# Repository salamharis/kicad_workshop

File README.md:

# KiCAD Workshop
Introduction on how to use KiCAD

Here the full slide for the workshop:
- [KiCAD Workshop Slides](https://docs.google.com/presentation/d/147WCcNicvjxVyRoyQiyZUYUu0onVnB6EPcWMXZ73EBk/edit?usp=sharing)

``` Disclaimer: This project only for educational purposes ```

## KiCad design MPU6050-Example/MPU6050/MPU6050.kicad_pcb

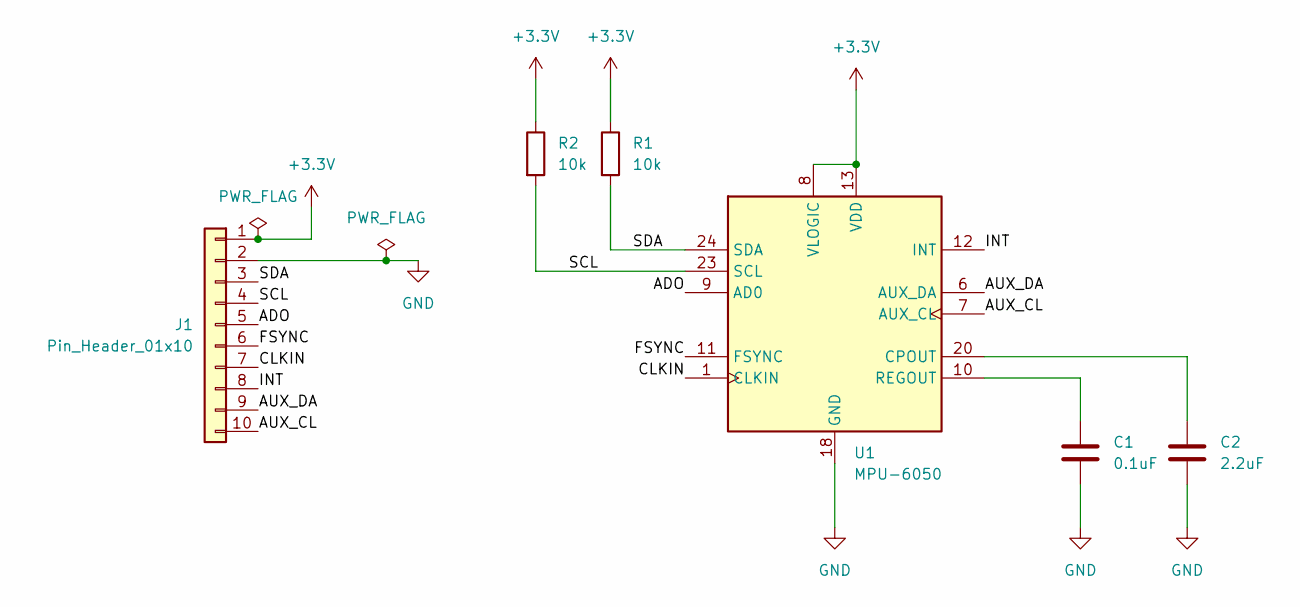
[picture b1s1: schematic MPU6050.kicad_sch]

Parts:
C1: 0.1uF; C_0603_1608Metric
C2: 2.2uF; C_0603_1608Metric
J1: Pin_Header_01x10; PinHeader_1x10_P2.54mm_Vertical
R1, R2: 10k; R_0603_1608Metric
U1: MPU-6050; InvenSense_QFN-24_4x4mm_P0.5mm

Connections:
+3.3V: J1.1, R1.1, R2.1, U1.8 (VLOGIC), U1.13 (VDD)
/ADO: J1.5, U1.9 (AD0)
/AUX_CL: J1.10, U1.7 (AUX_CL)
/AUX_DA: J1.9, U1.6 (AUX_DA)
/CLKIN: J1.7, U1.1 (CLKIN)
/FSYNC: J1.6, U1.11 (FSYNC)
/INT: J1.8, U1.12 (INT)
/SCL: J1.4, R2.2, U1.23 (SCL)
/SDA: J1.3, R1.2, U1.24 (SDA)
GND: C1.2, C2.2, J1.2, U1.18 (GND)
unnamed: C2.1, U1.20 (CPOUT)
unnamed: C1.1, U1.10 (REGOUT)

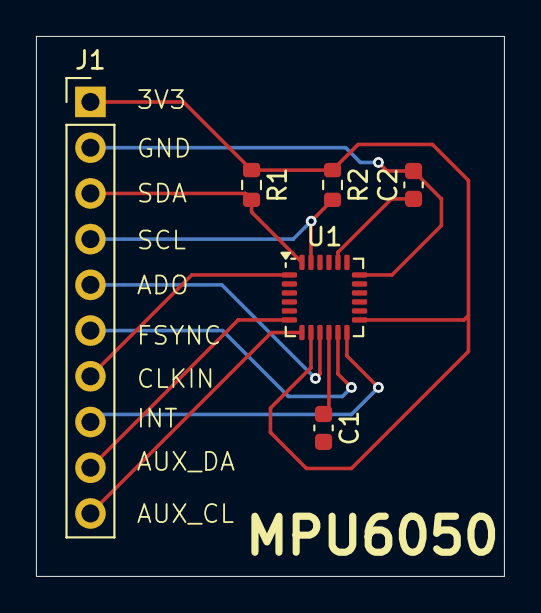
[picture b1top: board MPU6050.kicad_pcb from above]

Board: 2 copper layers, 26.0 x 30.0 mm, 6 parts (0 on the bottom side), 12 nets.

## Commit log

2024-05-04 added libraries and complete example
2024-05-04 remove backup files
2024-05-04 remove answer
2024-05-05 added answer & slide
